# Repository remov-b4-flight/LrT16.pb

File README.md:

# LrT16.pb
KiCAD project of 'LrT16' Print Circuit Board  
16 encodeer version of successor [LRTMAX](https://github.com/remov-b4-flight/LrTMAX)

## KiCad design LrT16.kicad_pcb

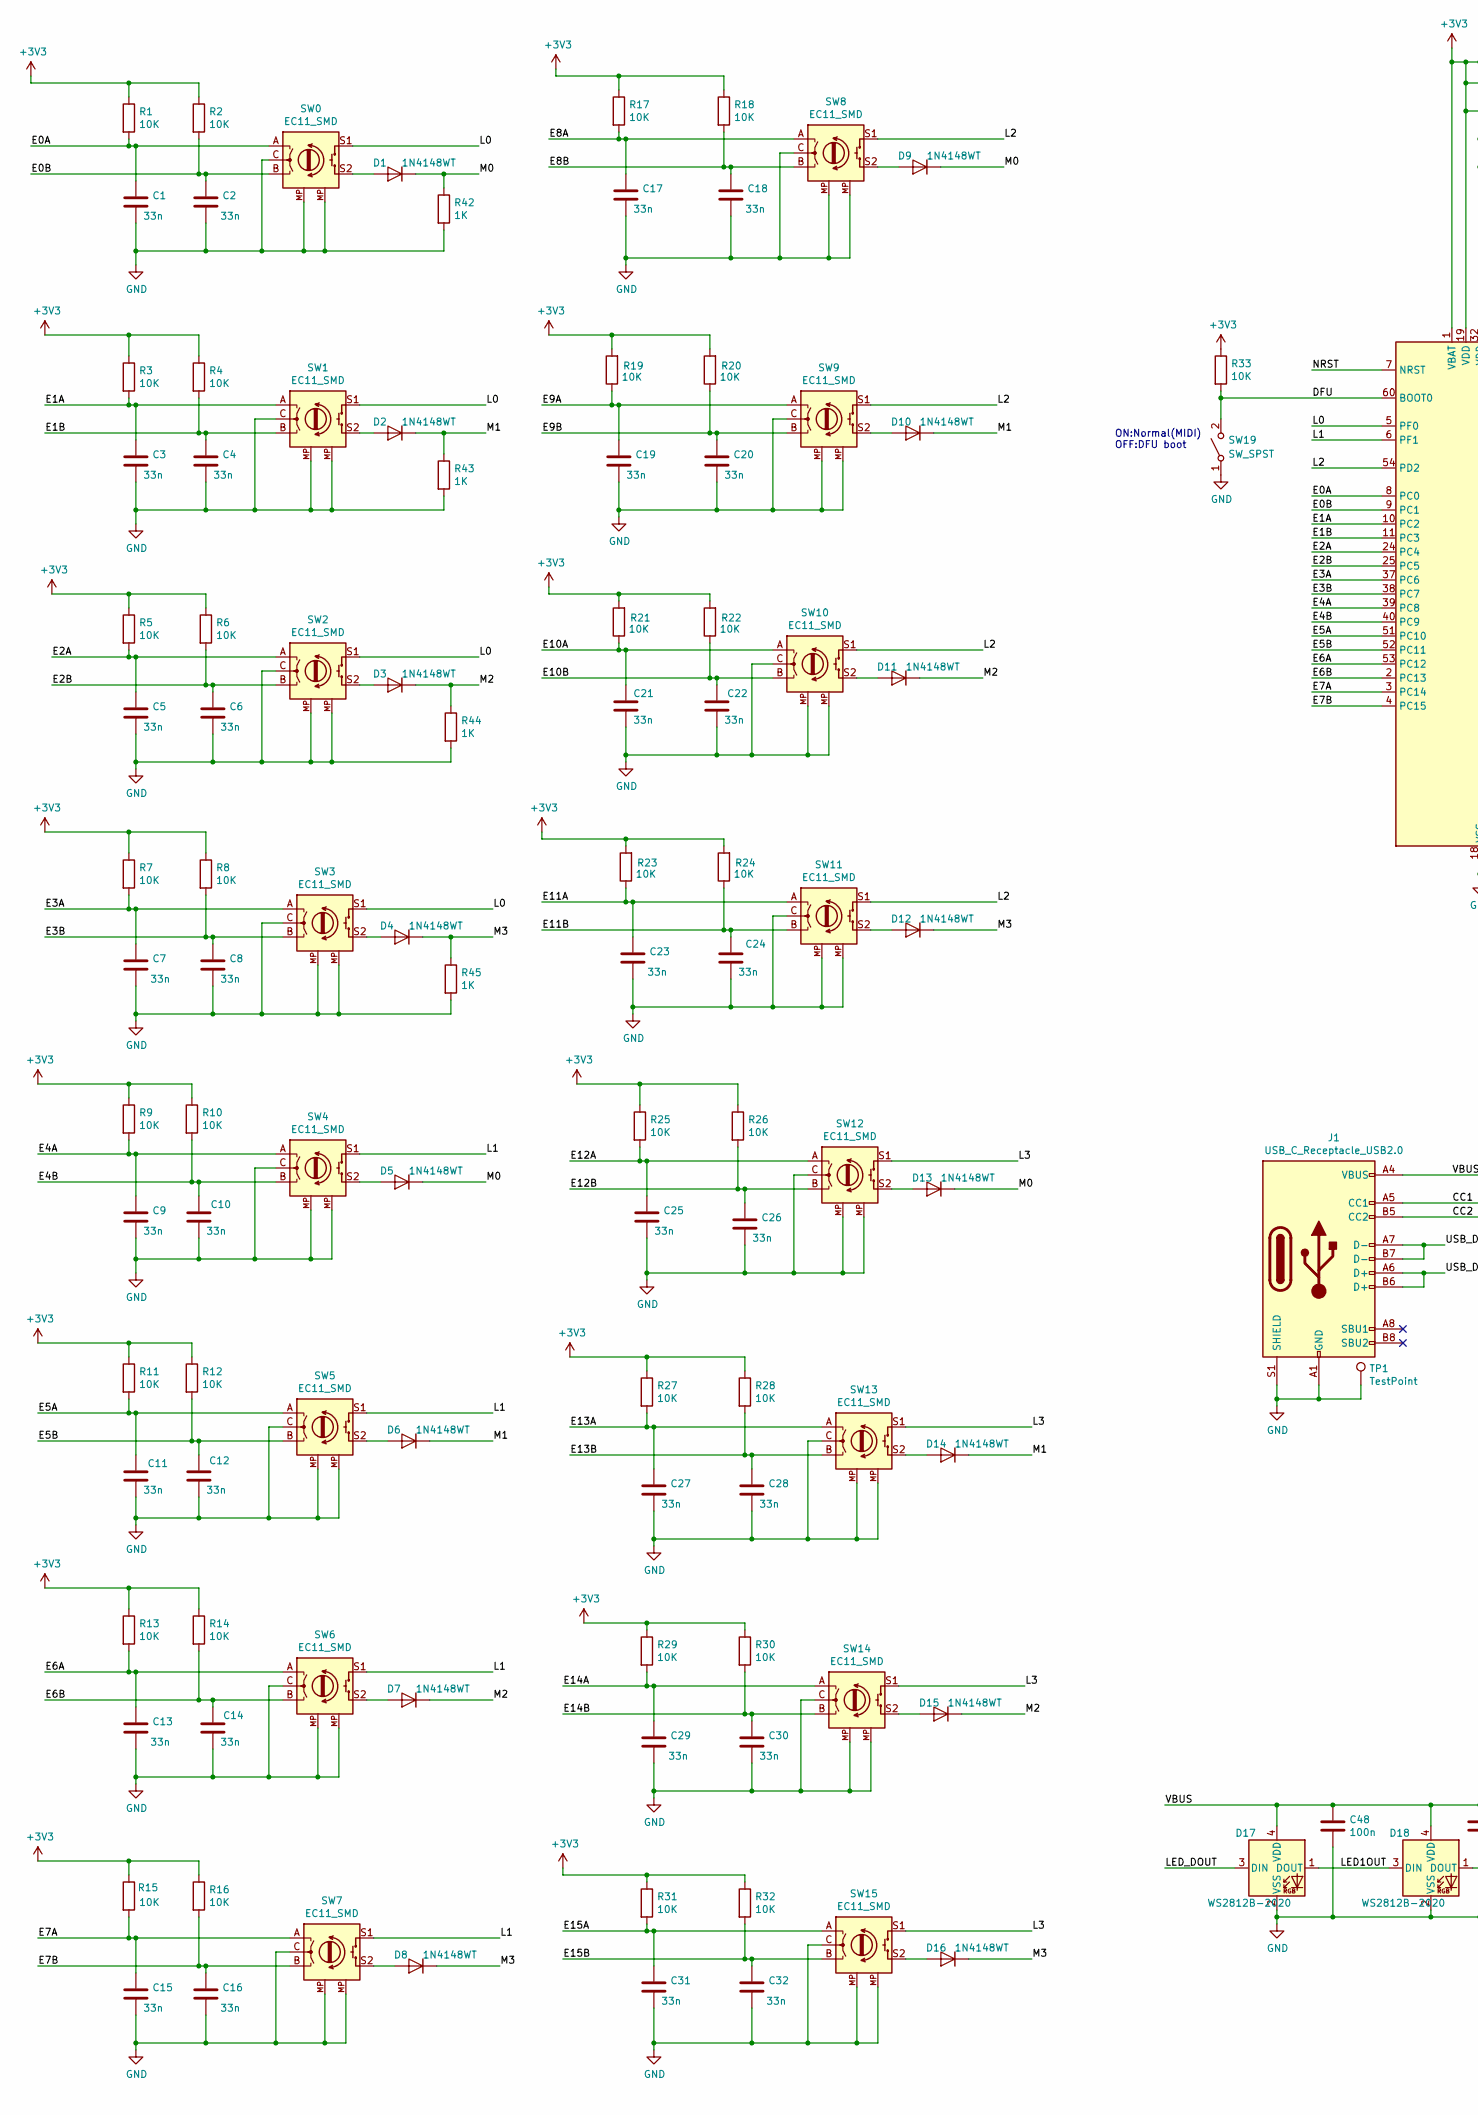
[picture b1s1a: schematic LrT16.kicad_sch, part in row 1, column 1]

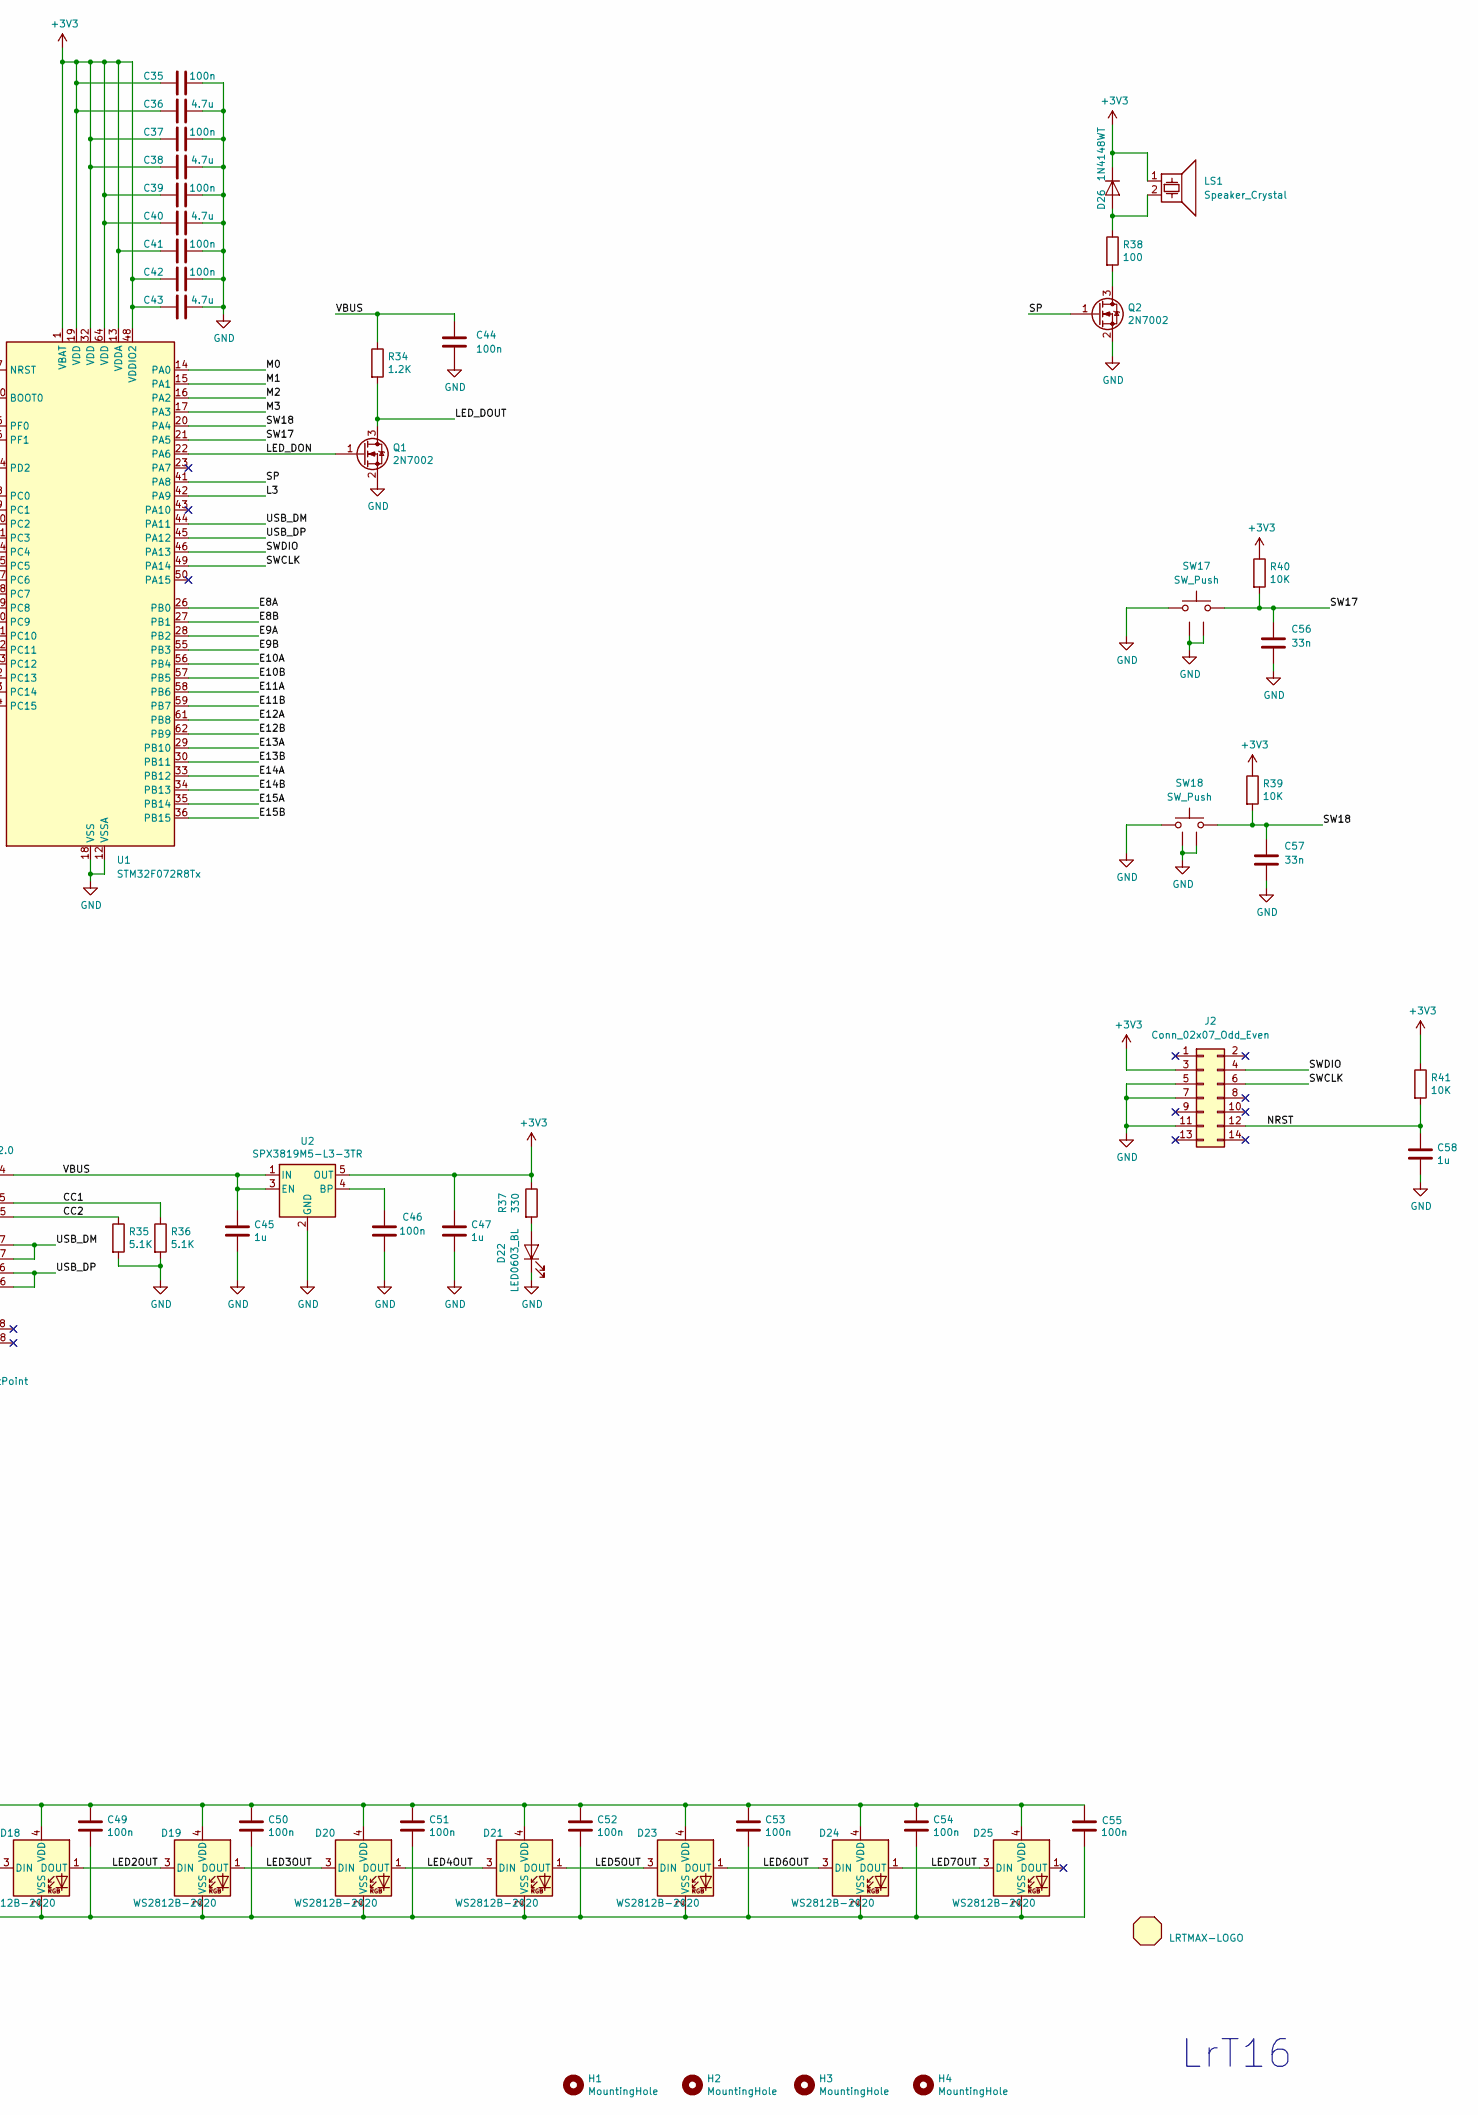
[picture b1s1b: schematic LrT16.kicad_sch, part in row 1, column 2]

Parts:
C1, C2, C3, C4, C5, C6, C7, C8, C9, C10, C11, C12, C13, C14, C15, C16, C17, C18, C19, C20, C21, C22, C23, C24, C25, C26, C27, C28, C29, C30, C31, C32, C56, C57: 33n; C_0603_1608Metric
C35, C37, C39, C41, C42: 100n; C_0402_1005Metric
C36, C38, C40, C43: 4.7u; C_0402_1005Metric
C44, C48, C49, C50, C51, C52, C53, C54, C55: 100n; C_0603_1608Metric
C45, C47, C58: 1u; C_0805_2012Metric
C46: 100n; C_0805_2012Metric
D1, D2, D3, D4, D5, D6, D7, D8, D9, D10, D11, D12, D13, D14, D15, D16, D26: 1N4148WT; D_SOD-523
D17, D18, D19, D20, D21, D23, D24, D25: WS2812B-2020; LED_WS2812B-2020
D22: LED0603_BL; LED_0603_1608Metric_Pad1.05x0.95mm_HandSolder
H1, H2, H3, H4: MountingHole; MountingHole_2.7mm_M2.5
J1: USB_C_Receptacle_USB2.0; USB_C_Receptacle_HRO_TYPE-C-31-M-12
J2: Conn_02x07_Odd_Even; PinHeader_2x07_P1.27mm_Horizontal
LS1: Speaker_Crystal; UGCT7525AN4
Q1, Q2: 2N7002; SOT-23
R1, R2, R3, R4, R5, R6, R7, R8, R9, R10, R11, R12, R13, R14, R15, R16, R17, R18, R19, R20, R21, R22, R23, R24, R25, R26, R27, R28, R29, R30, R31, R32, R33, R39, R40, R41: 10K; R_0603_1608Metric
R34: 1.2K; R_0805_2012Metric
R35, R36: 5.1K; R_0402_1005Metric
R37: 330; R_0805_2012Metric_Pad1.20x1.40mm_HandSolder
R38: 100; R_0805_2012Metric_Pad1.20x1.40mm_HandSolder
R42, R43, R44, R45: 1K; R_0603_1608Metric
REF01: LRTMAX-LOGO; LrTMAX-LOGO
SW0, SW1, SW2, SW3, SW4, SW5, SW6, SW7, SW8, SW9, SW10, SW11, SW12, SW13, SW14, SW15: EC11_SMD; RotaryEncoder_Alps_EC11E-Switch_Vertical_H20mm
SW17, SW18: SW_Push; SKHLLAA010
SW19: SW_SPST; SW_DIP_SPSTx01_Slide_6.7x4.1mm_W7.62mm_P2.54mm_LowProfile
TP1: TestPoint; TestPoint_THTPad_D1.0mm_Drill0.5mm
U1: STM32F072R8Tx; LQFP-64_10x10mm_P0.5mm
U2: SPX3819M5-L3-3TR; SOT-23-5

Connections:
+3V3: C35.2, C36.2, C37.2, C38.2, C39.2, C40.2, C41.2, C42.2, C43.2, C47.1, D26.1 (K), J2.3, LS1.1, R1.1, R2.1, R3.1, R4.1, R5.1, R6.1, R7.1, R8.1, R9.1, R10.1, R11.1, R12.1, R13.1, R14.1, R15.1, R16.1, R17.1, R18.1, R19.2, R20.2, R21.2, R22.2, R23.2, R24.2, R25.1, R26.1, R27.1, R28.1, R29.1, R30.1, R31.1, R32.1, R33.1, R37.1, R39.1, R40.1, R41.1, U1.1 (VBAT), U1.13 (VDDA), U1.19 (VDD), U1.32 (VDD), U1.48 (VDDIO2), U1.64 (VDD), U2.5 (OUT)
/CC1: J1.A5 (CC1), R36.1
/CC2: J1.B5 (CC2), R35.1
/DFU: R33.2, SW19.2 (B), U1.60 (BOOT0)
/E0A: C1.1, R1.2, SW0.A, U1.8 (PC0)
/E0B: C2.1, R2.2, SW0.B, U1.9 (PC1)
/E1A: C3.1, R3.2, SW1.A, U1.10 (PC2)
/E1B: C4.1, R4.2, SW1.B, U1.11 (PC3)
/E2A: C5.1, R5.2, SW2.A, U1.24 (PC4)
/E2B: C6.1, R6.2, SW2.B, U1.25 (PC5)
/E3A: C7.1, R7.2, SW3.A, U1.37 (PC6)
/E3B: C8.1, R8.2, SW3.B, U1.38 (PC7)
/E4A: C9.1, R9.2, SW4.A, U1.39 (PC8)
/E4B: C10.1, R10.2, SW4.B, U1.40 (PC9)
/E5A: C11.1, R11.2, SW5.A, U1.51 (PC10)
/E5B: C12.1, R12.2, SW5.B, U1.52 (PC11)
/E6A: C13.1, R13.2, SW6.A, U1.53 (PC12)
/E6B: C14.1, R14.2, SW6.B, U1.2 (PC13)
/E7A: C15.1, R15.2, SW7.A, U1.3 (PC14)
/E7B: C16.1, R16.2, SW7.B, U1.4 (PC15)
/E8A: C17.1, R17.2, SW8.A, U1.26 (PB0)
/E8B: C18.1, R18.2, SW8.B, U1.27 (PB1)
/E9A: C19.1, R19.1, SW9.A, U1.28 (PB2)
/E9B: C20.1, R20.1, SW9.B, U1.55 (PB3)
/E10A: C21.1, R21.1, SW10.A, U1.56 (PB4)
/E10B: C22.1, R22.1, SW10.B, U1.57 (PB5)
/E11A: C23.1, R23.1, SW11.A, U1.58 (PB6)
/E11B: C24.1, R24.1, SW11.B, U1.59 (PB7)
/E12A: C25.1, R25.2, SW12.A, U1.61 (PB8)
/E12B: C26.1, R26.2, SW12.B, U1.62 (PB9)
/E13A: C27.1, R27.2, SW13.A, U1.29 (PB10)
/E13B: C28.1, R28.2, SW13.B, U1.30 (PB11)
/E14A: C29.1, R29.2, SW14.A, U1.33 (PB12)
/E14B: C30.1, R30.2, SW14.B, U1.34 (PB13)
/E15A: C31.1, R31.2, SW15.A, U1.35 (PB14)
/E15B: C32.1, R32.2, SW15.B, U1.36 (PB15)
/L0: SW0.S1, SW1.S1, SW2.S1, SW3.S1, U1.5 (PF0)
/L1: SW4.S1, SW5.S1, SW6.S1, SW7.S1, U1.6 (PF1)
/L2: SW8.S1, SW9.S1, SW10.S1, SW11.S1, U1.54 (PD2)
/L3: SW12.S1, SW13.S1, SW14.S1, SW15.S1, U1.42 (PA9)
/LED1OUT: D17.1 (DOUT), D18.3 (DIN)
/LED2OUT: D18.1 (DOUT), D19.3 (DIN)
/LED3OUT: D19.1 (DOUT), D20.3 (DIN)
/LED4OUT: D20.1 (DOUT), D21.3 (DIN)
/LED5OUT: D21.1 (DOUT), D23.3 (DIN)
/LED6OUT: D23.1 (DOUT), D24.3 (DIN)
/LED7OUT: D24.1 (DOUT), D25.3 (DIN)
/LED_DON: Q1.1 (G), U1.22 (PA6)
/LED_DOUT: D17.3 (DIN), Q1.3 (D), R34.2
/M0: D1.1 (K), D5.1 (K), D9.1 (K), D13.1 (K), R42.1, U1.14 (PA0)
/M1: D2.1 (K), D6.1 (K), D10.1 (K), D14.1 (K), R43.1, U1.15 (PA1)
/M2: D3.1 (K), D7.1 (K), D11.1 (K), D15.1 (K), R44.1, U1.16 (PA2)
/M3: D4.1 (K), D8.1 (K), D12.1 (K), D16.1 (K), R45.1, U1.17 (PA3)
/NRST: C58.1, J2.12, R41.2, U1.7 (NRST)
/SP: Q2.1 (G), U1.41 (PA8)
/SW17: C56.1, R40.2, SW17.2, U1.21 (PA5)
/SW18: C57.1, R39.2, SW18.1, U1.20 (PA4)
/SWCLK: J2.6, U1.49 (PA14)
/SWDIO: J2.4, U1.46 (PA13)
/USB_DM: J1.A7 (D-), J1.B7 (D-), U1.44 (PA11)
/USB_DP: J1.A6 (D+), J1.B6 (D+), U1.45 (PA12)
/VBUS: C44.1, C45.1, C48.1, C49.1, C50.1, C51.1, C52.1, C53.1, C54.1, C55.1, D17.4 (VDD), D18.4 (VDD), D19.4 (VDD), D20.4 (VDD), D21.4 (VDD), D23.4 (VDD), D24.4 (VDD), D25.4 (VDD), J1.A4 (VBUS), J1.A9 (VBUS), J1.B4 (VBUS), J1.B9 (VBUS), R34.1, U2.1 (IN), U2.3 (EN)
GND: C1.2, C2.2, C3.2, C4.2, C5.2, C6.2, C7.2, C8.2, C9.2, C10.2, C11.2, C12.2, C13.2, C14.2, C15.2, C16.2, C17.2, C18.2, C19.2, C20.2, C21.2, C22.2, C23.2, C24.2, C25.2, C26.2, C27.2, C28.2, C29.2, C30.2, C31.2, C32.2, C35.1, C36.1, C37.1, C38.1, C39.1, C40.1, C41.1, C42.1, C43.1, C44.2, C45.2, C46.2, C47.2, C48.2, C49.2, C50.2, C51.2, C52.2, C53.2, C54.2, C55.2, C56.2, C57.2, C58.2, D17.2 (VSS), D18.2 (VSS), D19.2 (VSS), D20.2 (VSS), D21.2 (VSS), D22.1 (K), D23.2 (VSS), D24.2 (VSS), D25.2 (VSS), J1.A1 (GND), J1.A12 (GND), J1.B1 (GND), J1.B12 (GND), J1.S1 (SHIELD), J2.5, J2.7, J2.11, Q1.2 (S), Q2.2 (S), R35.2, R36.2, R42.2, R43.2, R44.2, R45.2, SW0.C, SW0.MP (GND), SW1.C, SW1.MP (GND), SW2.C, SW2.MP (GND), SW3.C, SW3.MP (GND), SW4.C, SW4.MP (GND), SW5.C, SW5.MP (GND), SW6.C, SW6.MP (GND), SW7.C, SW7.MP (GND), SW8.C, SW8.MP (GND), SW9.C, SW9.MP (GND), SW10.C, SW10.MP (GND), SW11.C, SW11.MP (GND), SW12.C, SW12.MP (GND), SW13.C, SW13.MP (GND), SW14.C, SW14.MP (GND), SW15.C, SW15.MP (GND), SW17.1, SW17.G1, SW17.G2, SW18.2, SW18.G1, SW18.G2, SW19.1 (A), TP1.1, U1.12 (VSSA), U1.18 (VSS), U1.31 (VSS), U1.47 (VSS), U1.63 (VSS), U2.2 (GND)
unnamed: D1.2 (A), SW0.S2
unnamed: D2.2 (A), SW1.S2
unnamed: D3.2 (A), SW2.S2
unnamed: D4.2 (A), SW3.S2
unnamed: D5.2 (A), SW4.S2
unnamed: D6.2 (A), SW5.S2
unnamed: D7.2 (A), SW6.S2
unnamed: D8.2 (A), SW7.S2
unnamed: D9.2 (A), SW8.S2
unnamed: D10.2 (A), SW9.S2
unnamed: D11.2 (A), SW10.S2
unnamed: D12.2 (A), SW11.S2
unnamed: D13.2 (A), SW12.S2
unnamed: D14.2 (A), SW13.S2
unnamed: D15.2 (A), SW14.S2
unnamed: D16.2 (A), SW15.S2
unnamed: D22.2 (A), R37.2
unnamed: D26.2 (A), LS1.2, R38.1
unnamed: Q2.3 (D), R38.2
unnamed: C46.1, U2.4 (BP)

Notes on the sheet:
LrT16
ON:Normal(MIDI) OFF:DFU boot

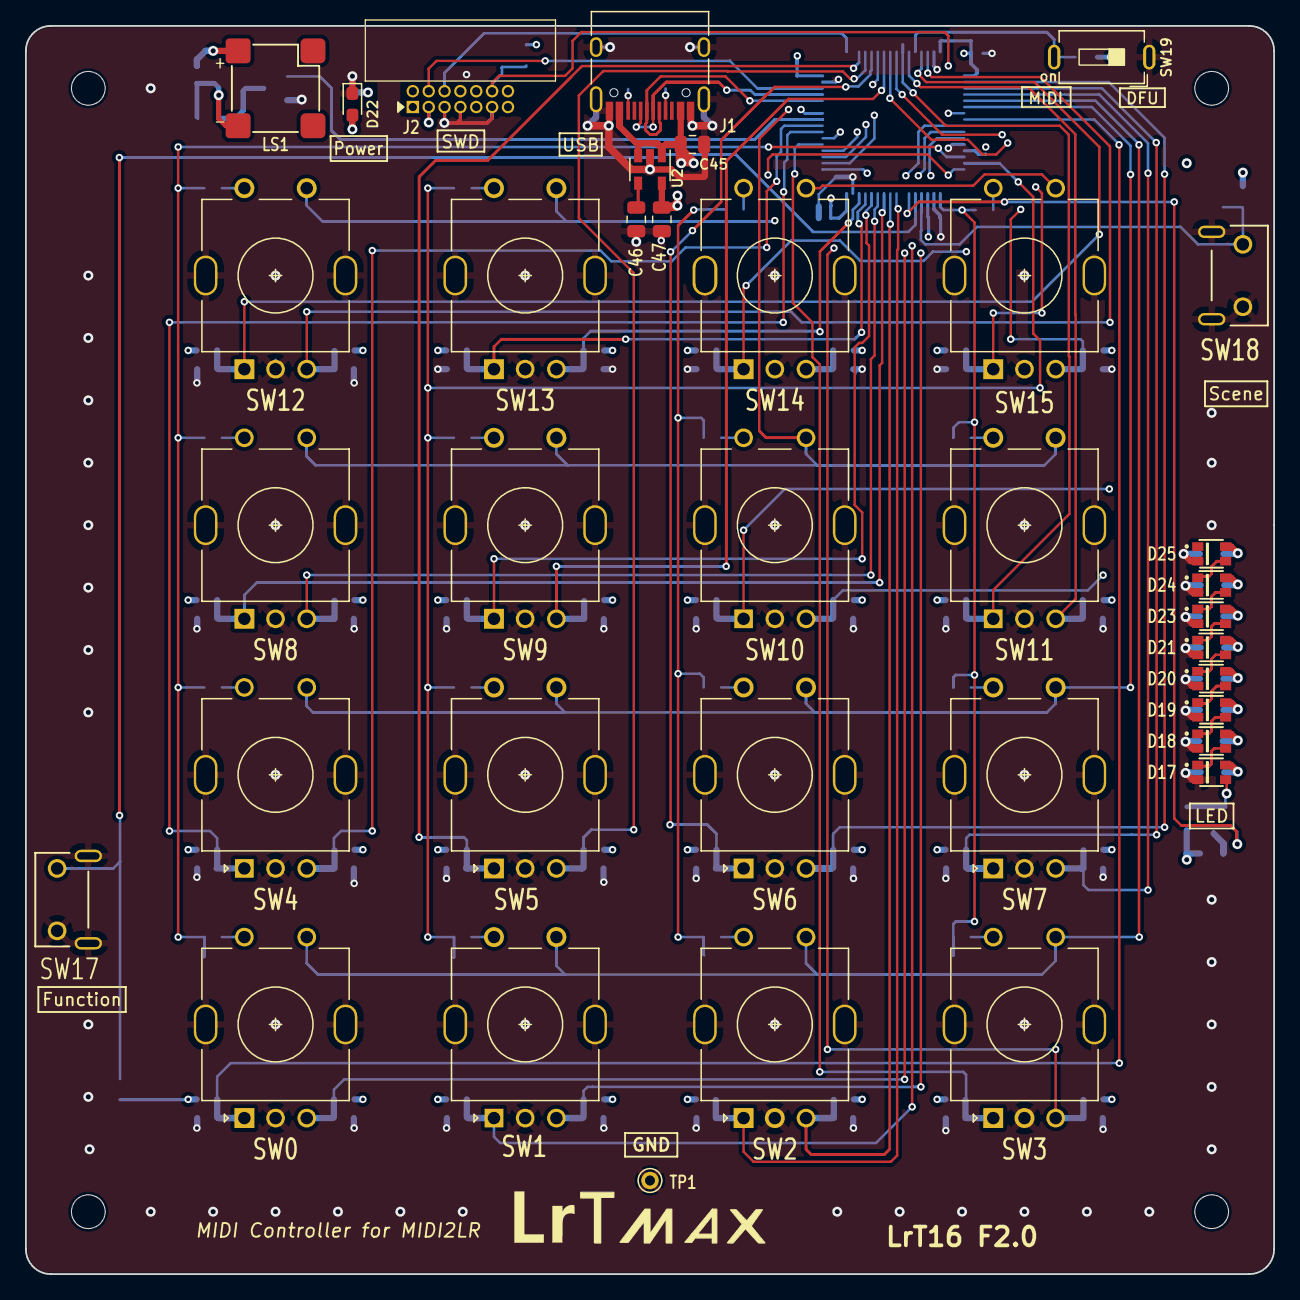
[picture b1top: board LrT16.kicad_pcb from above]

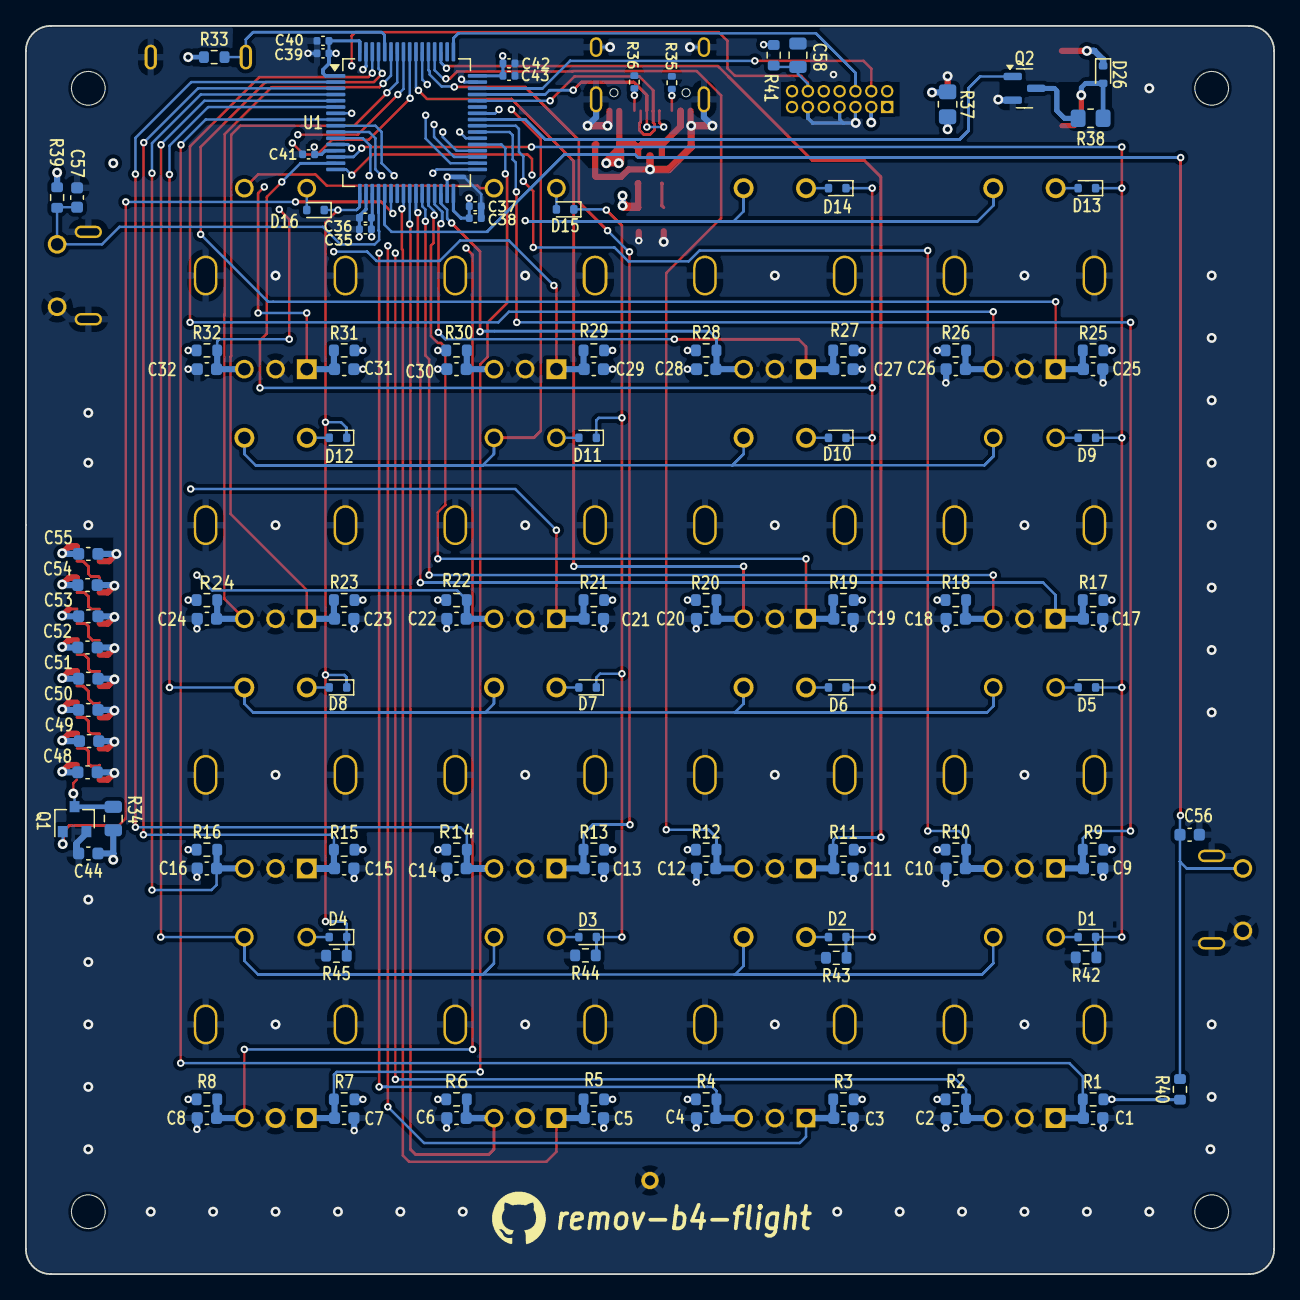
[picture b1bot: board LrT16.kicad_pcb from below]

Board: 4 copper layers, 100.0 x 100.0 mm, 159 parts (118 on the bottom side), 83 nets.

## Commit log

2026-03-21 LrT16.pb 1st commit
2026-03-21 Cleared DRC check
2026-03-21 edit .gitignore
2026-03-21 Errors & Warninngs are destroyed.
2026-03-21 Commited for board order
2026-03-21 Commited for boaard order #2
2026-03-21 Commit for order #3
2026-03-22 Commit #4 order (add SP)
2026-03-22 Commit for final F1.0 order
2026-03-22 edit README.md
2026-04-17 edit pcb pattern
2026-04-23 modify schematic for encoder
2026-04-23 fixed scematic for footprint on top side
2026-04-26 All wires are connected.
2026-04-26 Ready for PCB order
2026-04-27 Mod. switch debouncer
2026-04-27 clean up
2026-04-28 clean up2
2026-04-29 clean up 3
2026-05-01 Ready for F1.2 PCB order
2026-05-06 replace parts 1N4148WS to 1N4148WT due to JLCPCB message the does not fit into footprints.
2026-05-27 Fixed Circuits
2026-06-01 middle of PCB work
2026-06-02 middle trace drawing
2026-06-03 Working on LrT16.pb
2026-06-03 mod. J2 footprint
2026-06-03 reduce 3.3v fill area
2026-06-04 fix sylk error
2026-06-05 eliminate errors and warnings
2026-06-07 F2.0 board ordered.
